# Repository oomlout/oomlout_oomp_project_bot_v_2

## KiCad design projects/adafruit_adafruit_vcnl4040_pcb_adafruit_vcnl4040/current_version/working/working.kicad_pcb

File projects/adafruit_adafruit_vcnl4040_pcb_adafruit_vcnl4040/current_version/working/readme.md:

# adafruit_vcnl4040_pcb
 
## summary 
* id: adafruit_adafruit_vcnl4040_pcb_adafruit_vcnl4040
* user: adafruit
* name: adafruit_vcnl4040_pcb
* board: adafruit_vcnl4040
* repo: https://github.com/adafruit/Adafruit-VCNL4040-PCB

* src_file_repo_sch: 
* src_file_repo_sch_link: https://github.com/adafruit/Adafruit-VCNL4040-PCB/tree/master/
* full details link: https://github.com/oomlout/oomlout_oomp_project_bot_v_2/tree/main/projects/adafruit_adafruit_vcnl4040_pcb_adafruit_vcnl4040/current_version/working  

## schematic  
  
[schematic (pdf)](working_schematic.pdf) 

## pcb  

[board (pdf)](working.pdf)  

## working_bom
| Id | Designator | Footprint | Quantity | Designation | Supplier and ref |  | None | 
| --- | --- | --- | --- | --- | --- | --- | --- | 
| 1 | FID4,FID3 | FIDUCIAL_1MM | 2 | FIDUCIAL_1MM |  |  | [''] | 
| 2 | D1 | CHIPLED_0603_NOOUTLINE | 1 | GREEN |  |  | [''] | 
| 3 | U$1,U$19,U$21,U$17 | MOUNTINGHOLE_2.5_PLATED | 4 | MOUNTINGHOLE2.5 |  |  | [''] | 
| 4 | U$22 | ADAFRUIT_3.5MM | 1 |  |  |  | [''] | 
| 5 | CONN4,CONN3 | JST_SH4 | 2 | STEMMA_I2C_QT |  |  | [''] | 
| 6 | C2,C3 | 0805-NO | 2 | 10uF |  |  | [''] | 
| 7 | C1 | 0603-NO | 1 | 0.1uF |  |  | [''] | 
| 8 | U2 | SOT23-5 | 1 | AP2112K-3.3 |  |  | [''] | 
| 9 | U3 | VISHAY_VCNL4040_4X2X1.1 | 1 | VCNL4040M3OE |  |  | [''] | 
| 10 | R1 | 0603-NO | 1 | 10K |  |  | [''] | 
| 11 | Q2 | SOT363 | 1 | BSS138 |  |  | [''] | 
| 12 | JP1 | 1X06_ROUND_70 | 1 |  |  |  | [''] | 
| 13 | R3 | RESPACK_4X0603 | 1 | 10K |  |  | [''] | 
| 14 | U$25 | PCBFEAT-REV-040 | 1 |  |  |  | [''] | 
| 15 | U$31,U$30 | STEMMAQT | 2 |  |  |  | [''] | 

## bom_schematic
| Ref | Qnty | Value | Cmp name | Footprint | Description | Vendor | DNP | 
| --- | --- | --- | --- | --- | --- | --- | --- | 
| C1 | 1 | 0.1uF | CAP_CERAMIC0603_NO | working:0603-NO |  |  |  | 
| C2, C3 | 2 | 10uF | CAP_CERAMIC0805-NOOUTLINE | working:0805-NO |  |  |  | 
| CONN3, CONN4 | 2 | STEMMA_I2C_QT | STEMMA_I2C_QT | working:JST_SH4 |  |  |  | 
| D1 | 1 | GREEN | LED0603_NOOUTLINE | working:CHIPLED_0603_NOOUTLINE |  |  |  | 
| FID3, FID4 | 2 | FIDUCIAL_1MM | FIDUCIAL_1MM | working:FIDUCIAL_1MM |  |  |  | 
| JP1 | 1 | HEADER-1X670MIL | HEADER-1X670MIL | working:1X06_ROUND_70 |  |  |  | 
| Q2 | 1 | BSS138 | MOSFET-N_DUAL | working:SOT363 |  |  |  | 
| R1 | 1 | 10K | RESISTOR_0603_NOOUT | working:0603-NO |  |  |  | 
| R3 | 1 | 10K | RESISTOR_4PACK | working:RESPACK_4X0603 |  |  |  | 
| U2 | 1 | AP2112K-3.3 | VREG_SOT23-5 | working:SOT23-5 |  |  |  | 
| U3 | 1 | VCNL4040M3OE | VCNL4040M3OE | working:VISHAY_VCNL4040_4X2X1.1 |  |  |  | 
| U$1, U$17, U$19, U$21 | 4 | MOUNTINGHOLE2.5 | MOUNTINGHOLE2.5 | working:MOUNTINGHOLE_2.5_PLATED |  |  |  | 

## mounting_holes
| x | y | package | value | ref | size | 
| --- | --- | --- | --- | --- | --- | 
| 0.0 | 12.7 | MOUNTINGHOLE_2.5_PLATED | MOUNTINGHOLE2.5 | U$1 | m3 | 
| 20.32 | 12.7 | MOUNTINGHOLE_2.5_PLATED | MOUNTINGHOLE2.5 | U$17 | m3 | 
| 0.0 | 0.0 | MOUNTINGHOLE_2.5_PLATED | MOUNTINGHOLE2.5 | U$19 | m3 | 
| 20.32 | 0.0 | MOUNTINGHOLE_2.5_PLATED | MOUNTINGHOLE2.5 | U$21 | m3 |

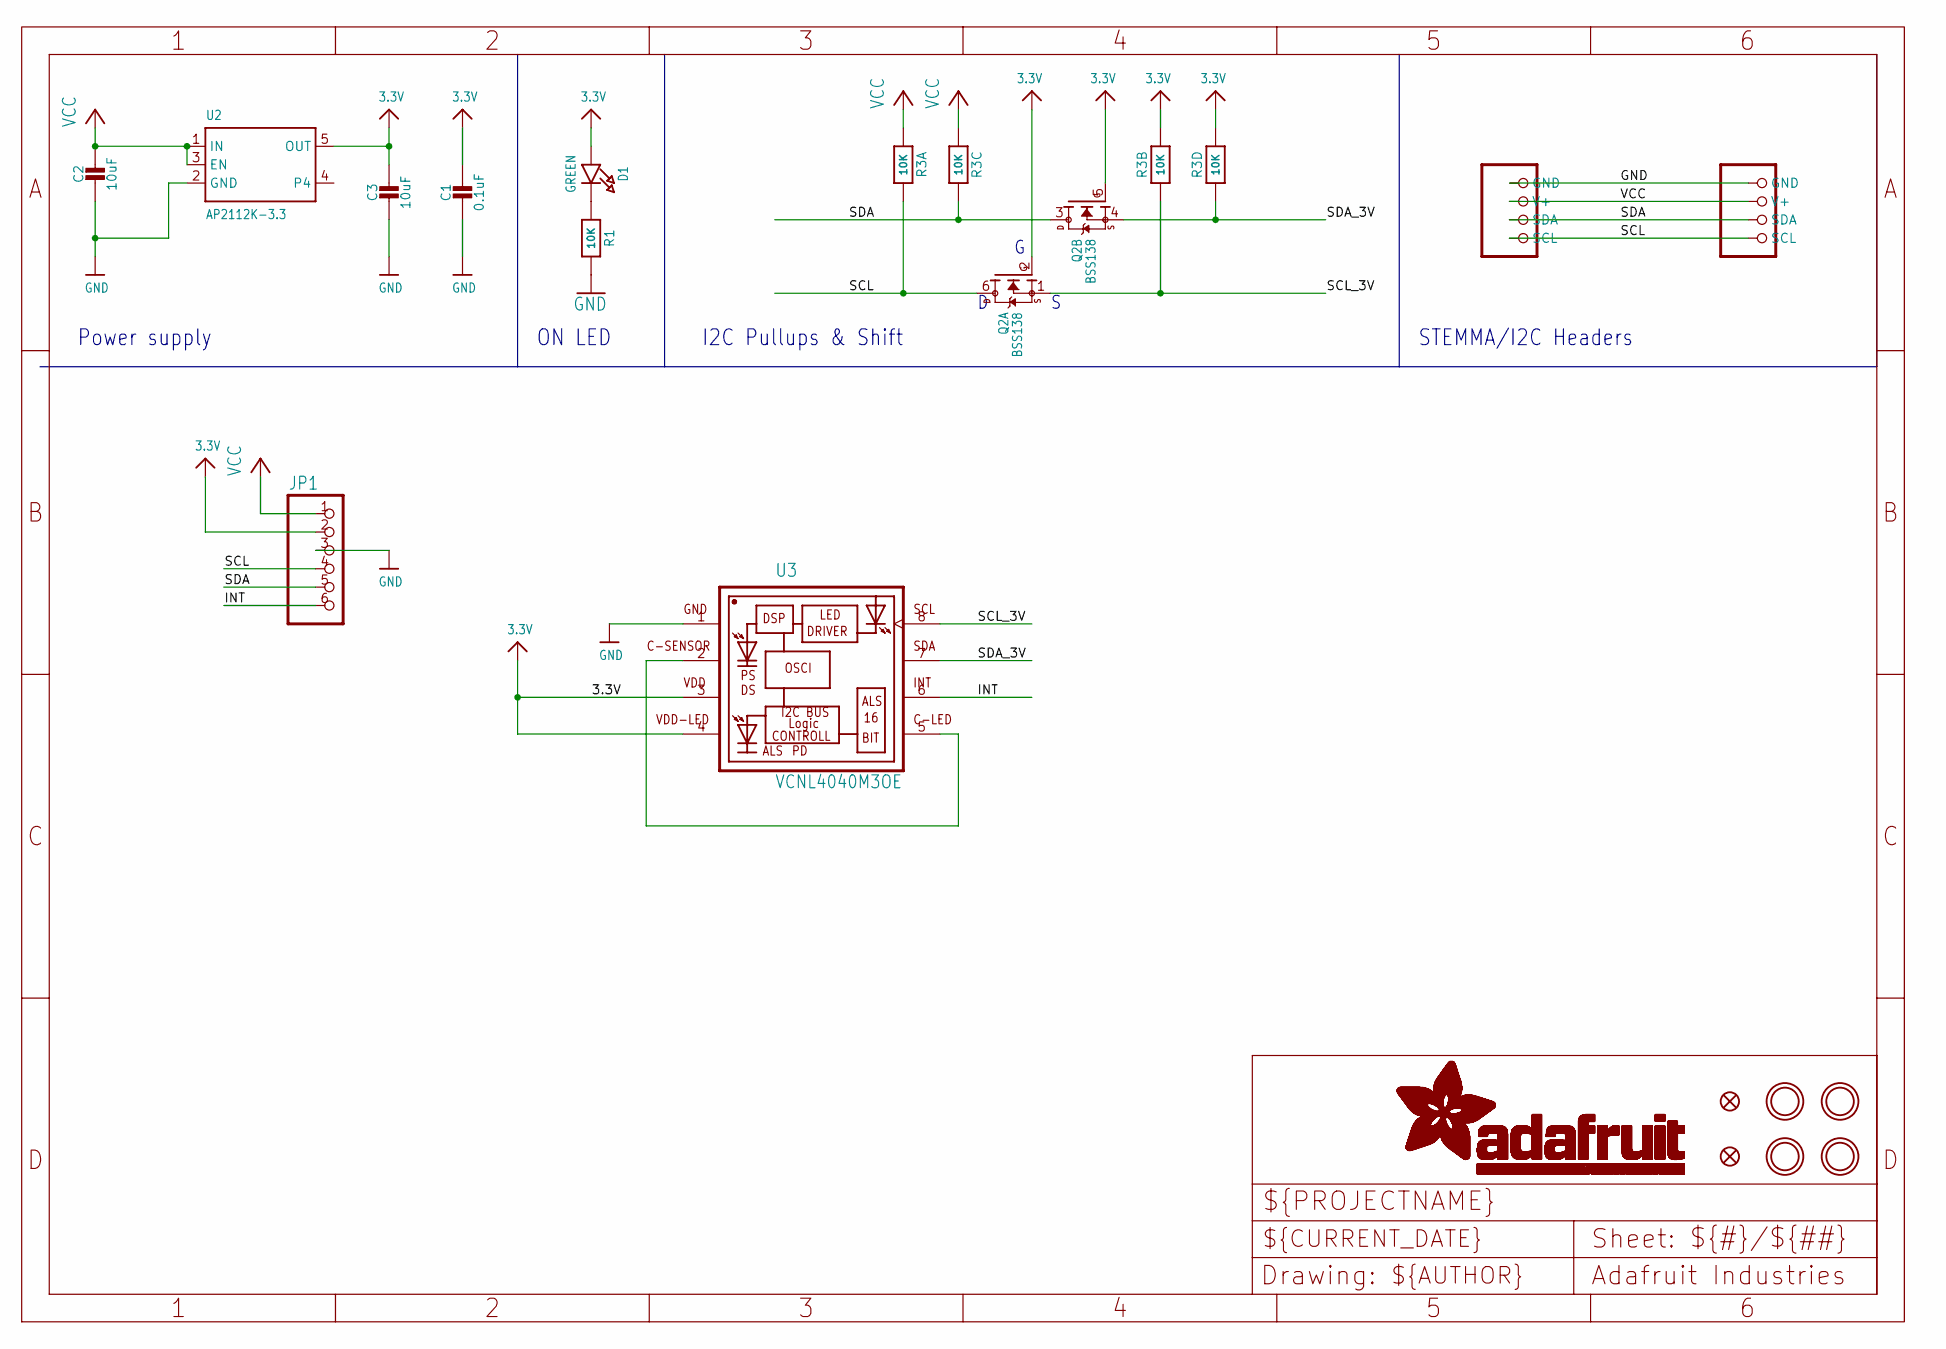
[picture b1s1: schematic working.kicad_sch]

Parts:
C1: 0.1uF; 0603-NO
C2, C3: 10uF; 0805-NO
CONN3, CONN4: STEMMA_I2C_QT; JST_SH4
D1: GREEN; CHIPLED_0603_NOOUTLINE
FID3, FID4: FIDUCIAL_1MM
JP1: HEADER-1X670MIL; 1X06_ROUND_70
Q2: BSS138; SOT363
R1: 10K; 0603-NO
R3: 10K; RESPACK_4X0603
U2: AP2112K-3.3; SOT23-5
U3: VCNL4040M3OE; VISHAY_VCNL4040_4X2X1.1
U$1, U$17, U$19, U$21: MOUNTINGHOLE2.5; MOUNTINGHOLE_2.5_PLATED

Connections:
3.3V: C1.1, C3.1, D1.A, JP1.2, Q2.2 (G), Q2.5 (G), R3.2 (1), R3.4 (1), U2.5 (OUT), U3.3 (VDD), U3.4 (VDD-LED)
CATHODE: U3.2 (C-SENSOR), U3.5 (C-LED)
GND: C1.2, C2.2, C3.2, CONN3.1 (GND), CONN4.1 (GND), JP1.3, R1.2, U2.2 (GND), U3.1 (GND)
INT: JP1.6, U3.6 (INT)
unnamed: D1.C, R1.1
SCL: CONN3.4 (SCL), CONN4.4 (SCL), JP1.4, Q2.6 (D), R3.8 (2)
SCL_3V: Q2.1 (S), R3.7 (2), U3.8 (SCL)
SDA: CONN3.3 (SDA), CONN4.3 (SDA), JP1.5, Q2.3 (D), R3.6 (2)
SDA_3V: Q2.4 (S), R3.5 (2), U3.7 (SDA)
VCC: C2.1, CONN3.2 (V+), CONN4.2 (V+), JP1.1, R3.1, R3.3 (1), U2.1 (IN), U2.3 (EN)

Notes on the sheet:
I2C Pullups & Shift
STEMMA/I2C Headers
ON LED
Power supply

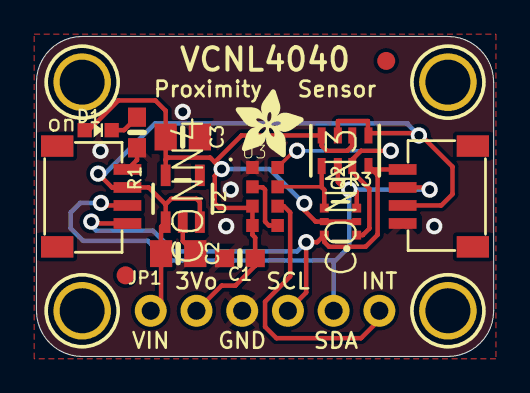
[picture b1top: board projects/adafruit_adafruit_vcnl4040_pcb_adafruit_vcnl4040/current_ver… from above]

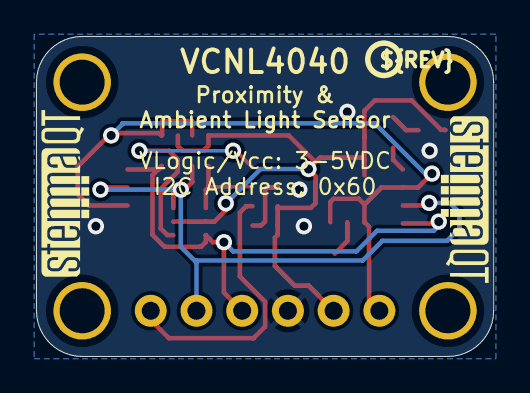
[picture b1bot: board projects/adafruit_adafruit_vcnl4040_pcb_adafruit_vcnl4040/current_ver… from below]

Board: 2 copper layers, 25.4 x 17.8 mm, 22 parts (3 on the bottom side), 10 nets.

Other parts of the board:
U$22: ADAFRUIT_3.5MM
U$25: PCBFEAT-REV-040
U$30, U$31: STEMMAQT

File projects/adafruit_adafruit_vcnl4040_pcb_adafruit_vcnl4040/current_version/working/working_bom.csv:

"Id";"Designator";"Footprint";"Quantity";"Designation";"Supplier and ref";
1;"FID4,FID3";"FIDUCIAL_1MM";2;"FIDUCIAL_1MM";;;
2;"D1";"CHIPLED_0603_NOOUTLINE";1;"GREEN";;;
3;"U$1,U$19,U$21,U$17";"MOUNTINGHOLE_2.5_PLATED";4;"MOUNTINGHOLE2.5";;;
4;"U$22";"ADAFRUIT_3.5MM";1;"";;;
5;"CONN4,CONN3";"JST_SH4";2;"STEMMA_I2C_QT";;;
6;"C2,C3";"0805-NO";2;"10uF";;;
7;"C1";"0603-NO";1;"0.1uF";;;
8;"U2";"SOT23-5";1;"AP2112K-3.3";;;
9;"U3";"VISHAY_VCNL4040_4X2X1.1";1;"VCNL4040M3OE";;;
10;"R1";"0603-NO";1;"10K";;;
11;"Q2";"SOT363";1;"BSS138";;;
12;"JP1";"1X06_ROUND_70";1;"";;;
13;"R3";"RESPACK_4X0603";1;"10K";;;
14;"U$25";"PCBFEAT-REV-040";1;"";;;
15;"U$31,U$30";"STEMMAQT";2;"";;;

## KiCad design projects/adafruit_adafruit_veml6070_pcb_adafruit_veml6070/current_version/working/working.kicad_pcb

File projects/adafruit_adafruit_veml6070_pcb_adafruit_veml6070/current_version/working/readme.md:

# adafruit_veml6070_pcb
 
## summary 
* id: adafruit_adafruit_veml6070_pcb_adafruit_veml6070
* user: adafruit
* name: adafruit_veml6070_pcb
* board: adafruit_veml6070
* repo: https://github.com/adafruit/Adafruit-VEML6070-PCB

* src_file_repo_sch: 
* src_file_repo_sch_link: https://github.com/adafruit/Adafruit-VEML6070-PCB/tree/master/
* full details link: https://github.com/oomlout/oomlout_oomp_project_bot_v_2/tree/main/projects/adafruit_adafruit_veml6070_pcb_adafruit_veml6070/current_version/working  

## schematic  
  
[schematic (pdf)](working_schematic.pdf) 

## pcb  

[board (pdf)](working.pdf)  

## working_bom
| Id | Designator | Footprint | Quantity | Designation | Supplier and ref |  | None | 
| --- | --- | --- | --- | --- | --- | --- | --- | 
| 1 | FID1 | FIDUCIAL_1MM | 1 | FIDUCIAL" |  |  | [''] | 
| 2 | U$11,U$10 | MOUNTINGHOLE_2.5_PLATED | 2 | MOUNTINGHOLE2.5 |  |  | [''] | 
| 3 | C1 | 0805-NO | 1 | 10uF |  |  | [''] | 
| 4 | U1 | VEML6070 | 1 | VEML6070 |  |  | [''] | 
| 5 | JP1 | 1X05_ROUND_70 | 1 |  |  |  | [''] | 
| 6 | R1,R4,R2 | 0805-NO | 3 | 10K |  |  | [''] | 
| 7 | R3 | 0805-NO | 1 | 270K |  |  | [''] | 
| 8 | U$2 | PCBFEAT-REV-040 | 1 |  |  |  | [''] | 
| 9 | U$14 | ADAFRUIT_2.5MM | 1 |  |  |  | [''] | 

## bom_schematic
| Ref | Qnty | Value | Cmp name | Footprint | Description | Vendor | DNP | 
| --- | --- | --- | --- | --- | --- | --- | --- | 
| C1 | 1 | 10uF | CAP_CERAMIC0805-NOOUTLINE | working:0805-NO |  |  |  | 
| FID1 | 1 | FIDUCIAL"" | FIDUCIAL{dblquote}{dblquote} | working:FIDUCIAL_1MM |  |  |  | 
| JP1 | 1 | HEADER-1X570MIL | HEADER-1X570MIL | working:1X05_ROUND_70 |  |  |  | 
| R1, R2, R4 | 3 | 10K | RESISTOR0805_NOOUTLINE | working:0805-NO |  |  |  | 
| R3 | 1 | 270K | RESISTOR0805_NOOUTLINE | working:0805-NO |  |  |  | 
| U1 | 1 | VEML6070 | UV_VEML6070 | working:VEML6070 |  |  |  | 
| U$10, U$11 | 2 | MOUNTINGHOLE2.5 | MOUNTINGHOLE2.5 | working:MOUNTINGHOLE_2.5_PLATED |  |  |  | 

## mounting_holes
| x | y | package | value | ref | size | 
| --- | --- | --- | --- | --- | --- | 
| 0.0 | 0.0 | MOUNTINGHOLE_2.5_PLATED | MOUNTINGHOLE2.5 | U$10 | m3 | 
| 7.62 | 0.0 | MOUNTINGHOLE_2.5_PLATED | MOUNTINGHOLE2.5 | U$11 | m3 |

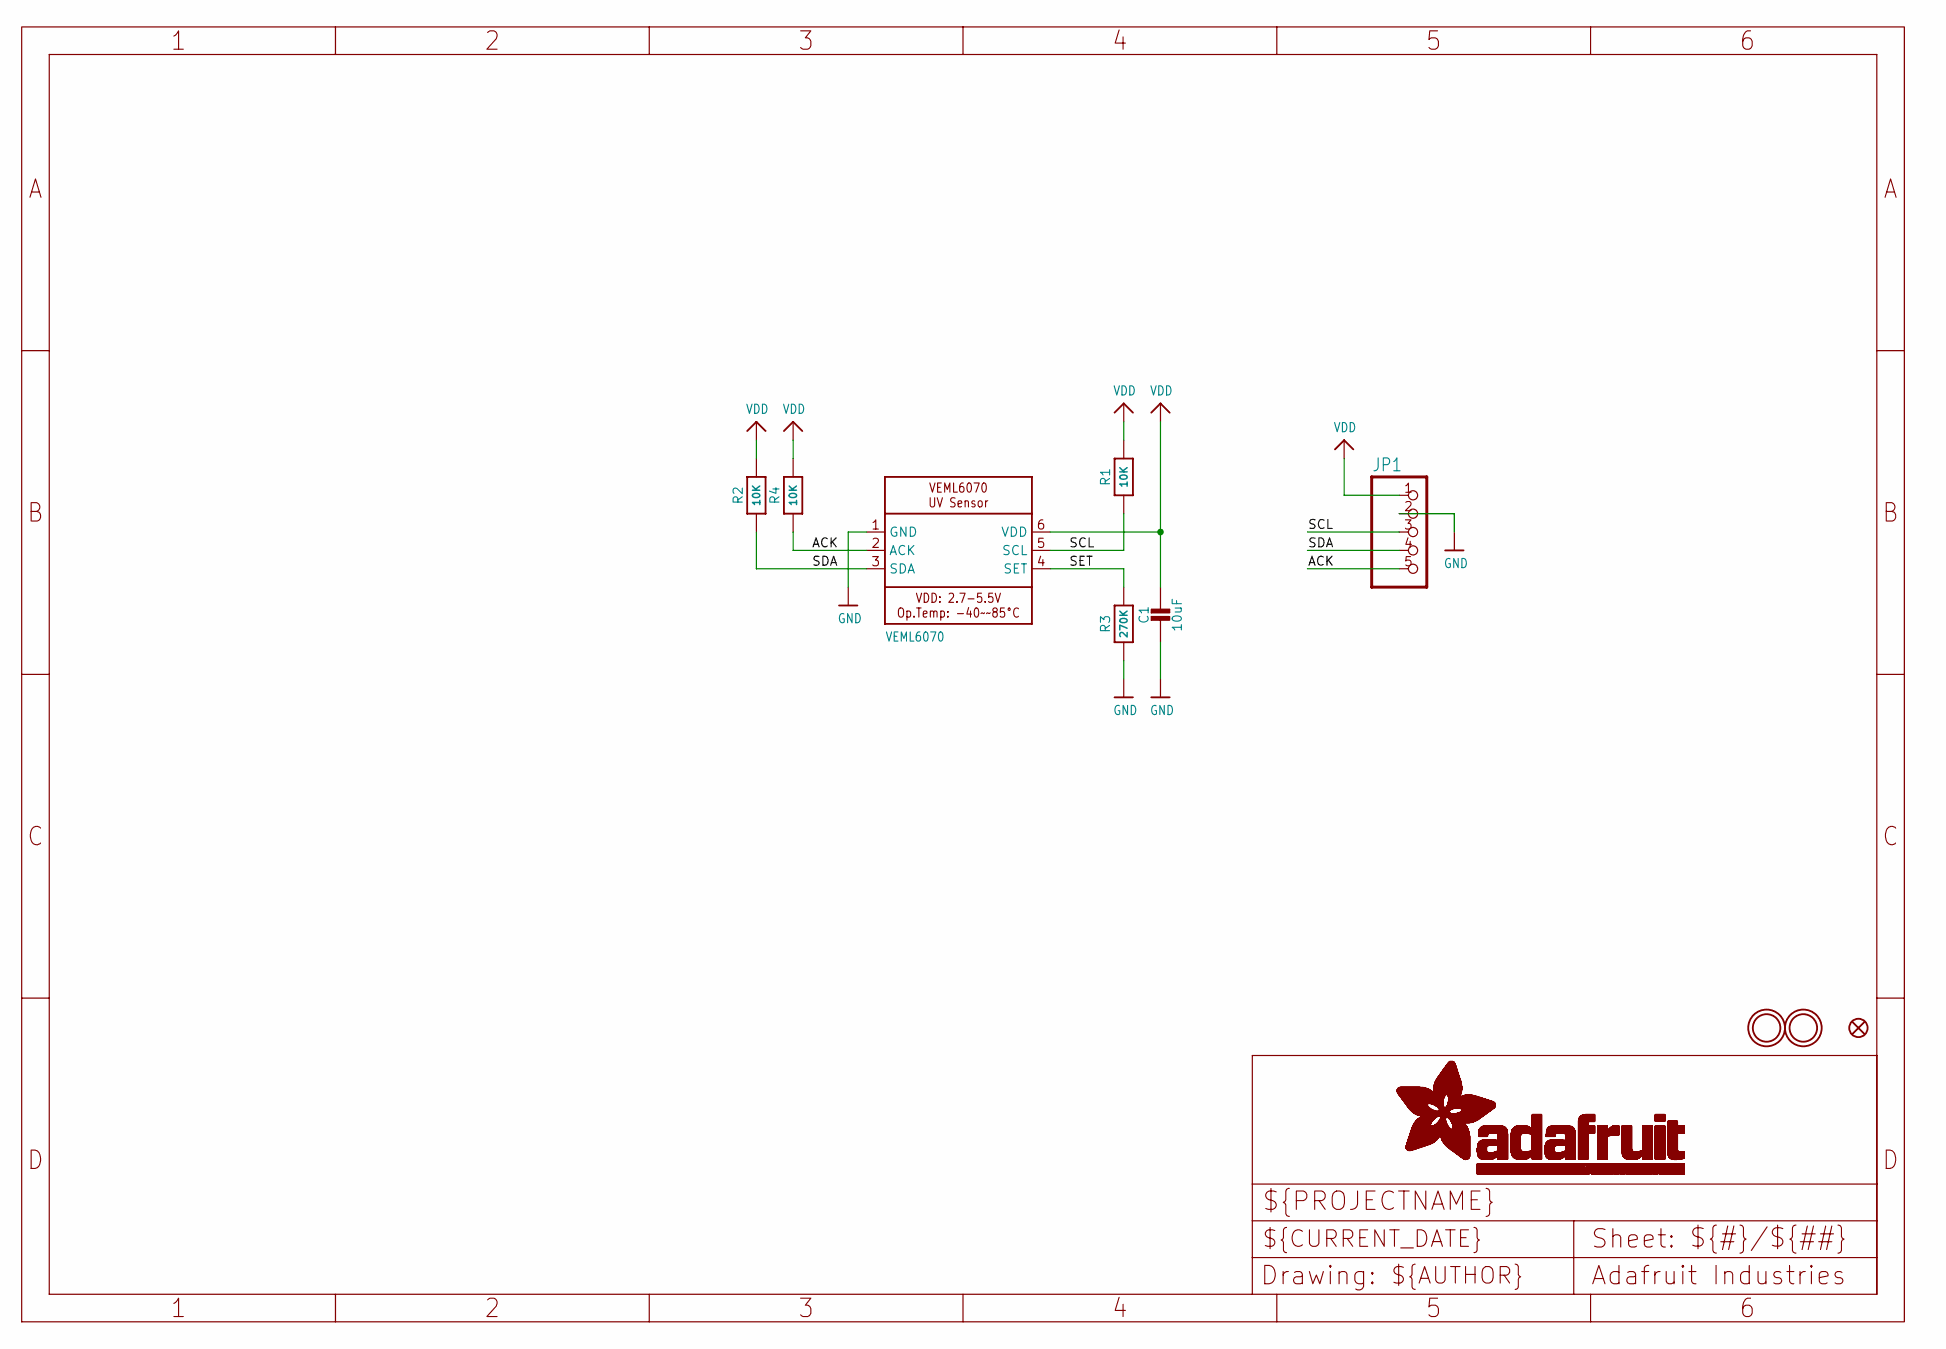
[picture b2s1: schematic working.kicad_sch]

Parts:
C1: 10uF; 0805-NO
FID1: FIDUCIAL""; FIDUCIAL_1MM
JP1: HEADER-1X570MIL; 1X05_ROUND_70
R1, R2, R4: 10K; 0805-NO
R3: 270K; 0805-NO
U1: VEML6070
U$10, U$11: MOUNTINGHOLE2.5; MOUNTINGHOLE_2.5_PLATED

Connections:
ACK: JP1.5, R4.1, U1.2 (ACK)
GND: C1.2, JP1.2, R3.1, U1.1 (GND)
SCL: JP1.3, R1.1, U1.5 (SCL)
SDA: JP1.4, R2.1, U1.3 (SDA)
SET: R3.2, U1.4 (SET)
VDD: C1.1, JP1.1, R1.2, R2.2, R4.2, U1.6 (VDD)

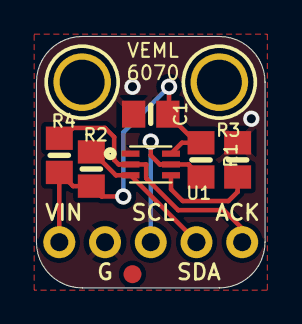
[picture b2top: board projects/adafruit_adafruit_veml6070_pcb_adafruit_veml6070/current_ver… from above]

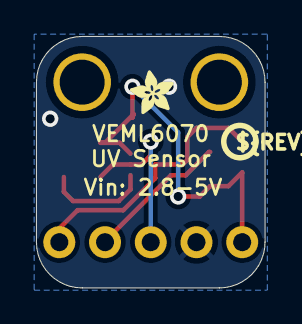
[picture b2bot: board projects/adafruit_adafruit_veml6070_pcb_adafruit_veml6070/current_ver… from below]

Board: 2 copper layers, 12.7 x 14.0 mm, 12 parts (2 on the bottom side), 6 nets.

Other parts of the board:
U$2: PCBFEAT-REV-040
U$14: ADAFRUIT_2.5MM

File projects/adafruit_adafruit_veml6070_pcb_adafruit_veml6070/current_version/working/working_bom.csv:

"Id";"Designator";"Footprint";"Quantity";"Designation";"Supplier and ref";
1;"FID1";"FIDUCIAL_1MM";1;"FIDUCIAL""";;;
2;"U$11,U$10";"MOUNTINGHOLE_2.5_PLATED";2;"MOUNTINGHOLE2.5";;;
3;"C1";"0805-NO";1;"10uF";;;
4;"U1";"VEML6070";1;"VEML6070";;;
5;"JP1";"1X05_ROUND_70";1;"";;;
6;"R1,R4,R2";"0805-NO";3;"10K";;;
7;"R3";"0805-NO";1;"270K";;;
8;"U$2";"PCBFEAT-REV-040";1;"";;;
9;"U$14";"ADAFRUIT_2.5MM";1;"";;;

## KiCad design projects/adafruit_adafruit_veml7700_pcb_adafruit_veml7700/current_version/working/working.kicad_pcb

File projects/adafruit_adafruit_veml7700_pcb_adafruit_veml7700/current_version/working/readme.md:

# adafruit_veml7700_pcb
 
## summary 
* id: adafruit_adafruit_veml7700_pcb_adafruit_veml7700
* user: adafruit
* name: adafruit_veml7700_pcb
* board: adafruit_veml7700
* repo: https://github.com/adafruit/Adafruit-VEML7700-PCB

* src_file_repo_sch: 
* src_file_repo_sch_link: https://github.com/adafruit/Adafruit-VEML7700-PCB/tree/master/
* full details link: https://github.com/oomlout/oomlout_oomp_project_bot_v_2/tree/main/projects/adafruit_adafruit_veml7700_pcb_adafruit_veml7700/current_version/working  

## schematic  
  
[schematic (pdf)](working_schematic.pdf) 

## pcb  

[board (pdf)](working.pdf)  

## working_bom
| Id | Designator | Footprint | Quantity | Designation | Supplier and ref |  | None | 
| --- | --- | --- | --- | --- | --- | --- | --- | 
| 1 | FID4,FID3 | FIDUCIAL_1MM | 2 | FIDUCIAL_1MM |  |  | [''] | 
| 2 | U$4,U$22 | ADAFRUIT_3.5MM | 2 |  |  |  | [''] | 
| 3 | U$21,U$17,U$1,U$19 | MOUNTINGHOLE_2.5_PLATED | 4 | MOUNTINGHOLE2.5 |  |  | [''] | 
| 4 | C3,C2 | 0805-NO | 2 | 10uF |  |  | [''] | 
| 5 | Q2 | SOT363 | 1 | BSS138 |  |  | [''] | 
| 6 | JP2 | 1X05_ROUND | 1 |  |  |  | [''] | 
| 7 | U2 | SOT23-5 | 1 | AP2112K-3.3 |  |  | [''] | 
| 8 | R1 | 0603-NO | 1 | 47K |  |  | [''] | 
| 9 | R3 | RESPACK_4X0603 | 1 | 4.7K |  |  | [''] | 
| 10 | C1 | 0603-NO | 1 | 0.1uF |  |  | [''] | 
| 11 | CONN4,CONN3 | JST_SH4 | 2 | STEMMA_I2C_QT |  |  | [''] | 
| 12 | IC1 | VEML7700 | 1 | VEML7700 |  |  | [''] | 
| 13 | D1 | CHIPLED_0603_NOOUTLINE | 1 | GREEN |  |  | [''] | 
| 14 | U$25 | PCBFEAT-REV-040 | 1 |  |  |  | [''] | 
| 15 | U$30,U$31 | STEMMAQT | 2 |  |  |  | [''] | 
| 16 | U$2 | KATTNI_STOP | 1 |  |  |  | [''] | 
| 17 | SJ1 | SOLDERJUMPER_CLOSEDWIRE | 1 |  |  |  | [''] | 

## bom_schematic
| Ref | Qnty | Value | Cmp name | Footprint | Description | Vendor | DNP | 
| --- | --- | --- | --- | --- | --- | --- | --- | 
| C1 | 1 | 0.1uF | CAP_CERAMIC0603_NO | working:0603-NO |  |  |  | 
| C2, C3 | 2 | 10uF | CAP_CERAMIC0805-NOOUTLINE | working:0805-NO |  |  |  | 
| CONN3, CONN4 | 2 | STEMMA_I2C_QT | STEMMA_I2C_QT | working:JST_SH4 |  |  |  | 
| D1 | 1 | GREEN | LED0603_NOOUTLINE | working:CHIPLED_0603_NOOUTLINE |  |  |  | 
| FID3, FID4 | 2 | FIDUCIAL_1MM | FIDUCIAL_1MM | working:FIDUCIAL_1MM |  |  |  | 
| IC1 | 1 | VEML7700 | VEML7700 | working:VEML7700 |  |  |  | 
| JP2 | 1 | HEADER-1X5ROUND | HEADER-1X5ROUND | working:1X05_ROUND |  |  |  | 
| Q2 | 1 | BSS138 | MOSFET-N_DUAL | working:SOT363 |  |  |  | 
| R1 | 1 | 47K | RESISTOR_0603_NOOUT | working:0603-NO |  |  |  | 
| R3 | 1 | 4.7K | RESISTOR_4PACK | working:RESPACK_4X0603 |  |  |  | 
| SJ1 | 1 | SOLDERJUMPER_CLOSED | SOLDERJUMPER_CLOSED | working:SOLDERJUMPER_CLOSEDWIRE |  |  |  | 
| U2 | 1 | AP2112K-3.3 | VREG_SOT23-5 | working:SOT23-5 |  |  |  | 
| U$1, U$17, U$19, U$21 | 4 | MOUNTINGHOLE2.5 | MOUNTINGHOLE2.5 | working:MOUNTINGHOLE_2.5_PLATED |  |  |  | 

## mounting_holes
| x | y | package | value | ref | size | 
| --- | --- | --- | --- | --- | --- | 
| 0.0 | 12.7 | MOUNTINGHOLE_2.5_PLATED | MOUNTINGHOLE2.5 | U$1 | m3 | 
| 20.32 | 12.7 | MOUNTINGHOLE_2.5_PLATED | MOUNTINGHOLE2.5 | U$17 | m3 | 
| 0.0 | 0.0 | MOUNTINGHOLE_2.5_PLATED | MOUNTINGHOLE2.5 | U$19 | m3 | 
| 20.32 | 0.0 | MOUNTINGHOLE_2.5_PLATED | MOUNTINGHOLE2.5 | U$21 | m3 |

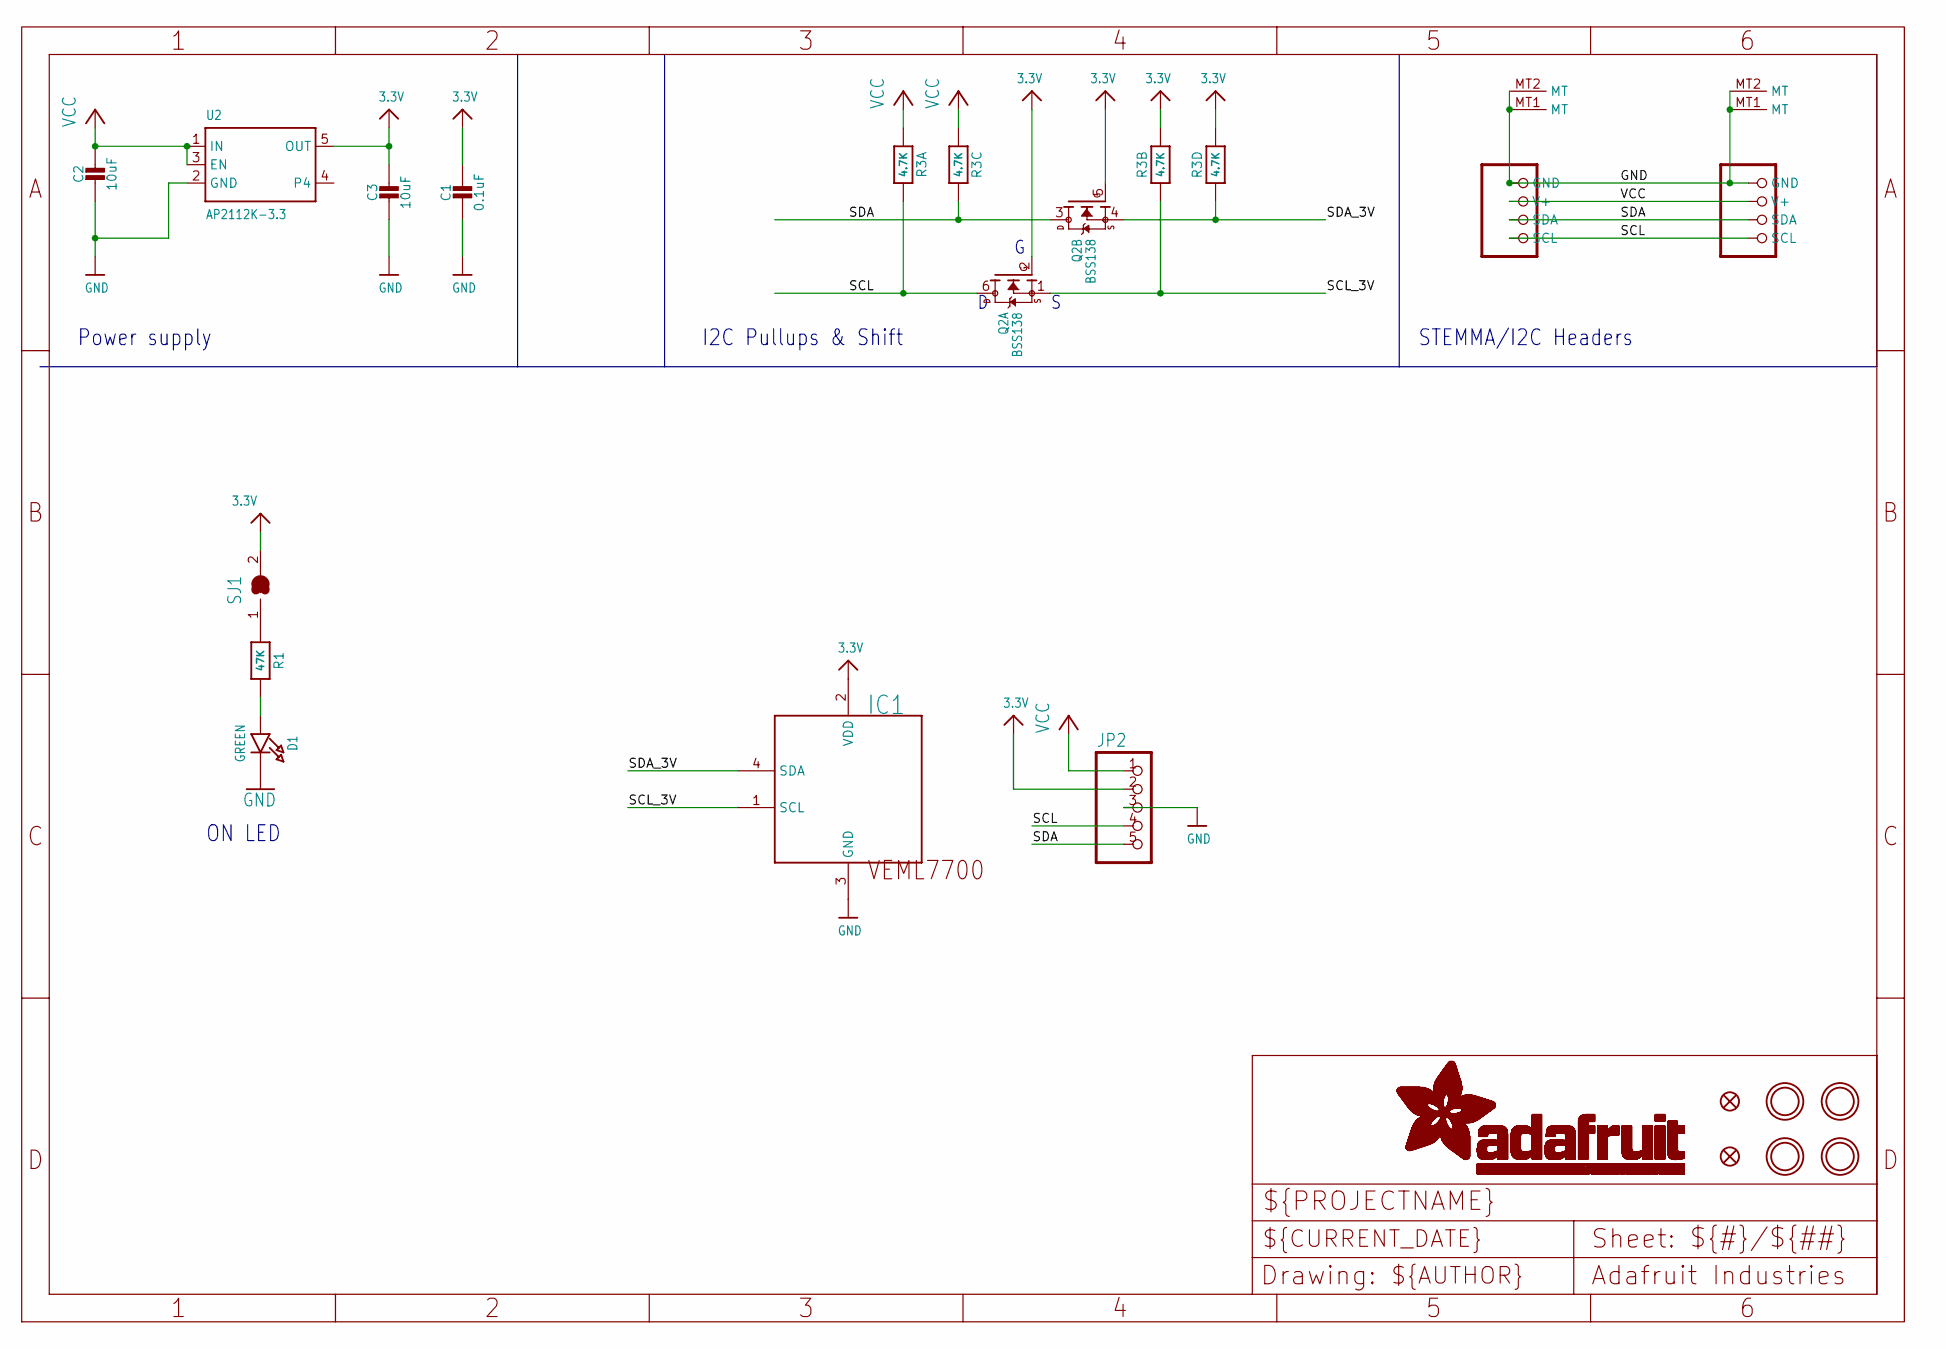
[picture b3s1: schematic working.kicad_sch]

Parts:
C1: 0.1uF; 0603-NO
C2, C3: 10uF; 0805-NO
CONN3, CONN4: STEMMA_I2C_QT; JST_SH4
D1: GREEN; CHIPLED_0603_NOOUTLINE
FID3, FID4: FIDUCIAL_1MM
IC1: VEML7700
JP2: HEADER-1X5ROUND; 1X05_ROUND
Q2: BSS138; SOT363
R1: 47K; 0603-NO
R3: 4.7K; RESPACK_4X0603
SJ1: SOLDERJUMPER_CLOSED; SOLDERJUMPER_CLOSEDWIRE
U2: AP2112K-3.3; SOT23-5
U$1, U$17, U$19, U$21: MOUNTINGHOLE2.5; MOUNTINGHOLE_2.5_PLATED

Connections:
3.3V: C1.1, C3.1, IC1.2 (VDD), JP2.2, Q2.2 (G), Q2.5 (G), R3.2 (1), R3.4 (1), SJ1.2, U2.5 (OUT)
GND: C1.2, C2.2, C3.2, CONN3.1 (GND), CONN3.MT1 (MT), CONN3.MT2 (MT), CONN4.1 (GND), CONN4.MT1 (MT), CONN4.MT2 (MT), D1.C, IC1.3 (GND), JP2.3, U2.2 (GND)
unnamed: D1.A, R1.2
unnamed: R1.1, SJ1.1
SCL: CONN3.4 (SCL), CONN4.4 (SCL), JP2.4, Q2.6 (D), R3.8 (2)
SCL_3V: IC1.1 (SCL), Q2.1 (S), R3.7 (2)
SDA: CONN3.3 (SDA), CONN4.3 (SDA), JP2.5, Q2.3 (D), R3.6 (2)
SDA_3V: IC1.4 (SDA), Q2.4 (S), R3.5 (2)
VCC: C2.1, CONN3.2 (V+), CONN4.2 (V+), JP2.1, R3.1, R3.3 (1), U2.1 (IN), U2.3 (EN)

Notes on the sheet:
Power supply
ON LED
I2C Pullups & Shift
STEMMA/I2C Headers

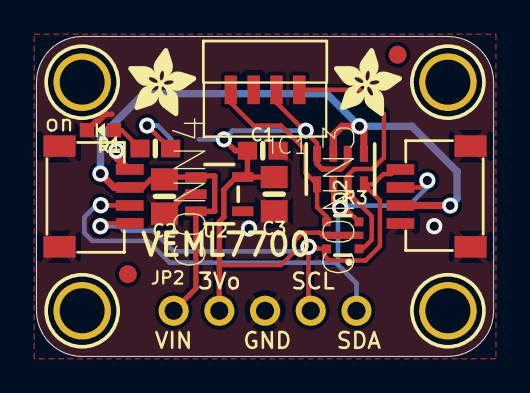
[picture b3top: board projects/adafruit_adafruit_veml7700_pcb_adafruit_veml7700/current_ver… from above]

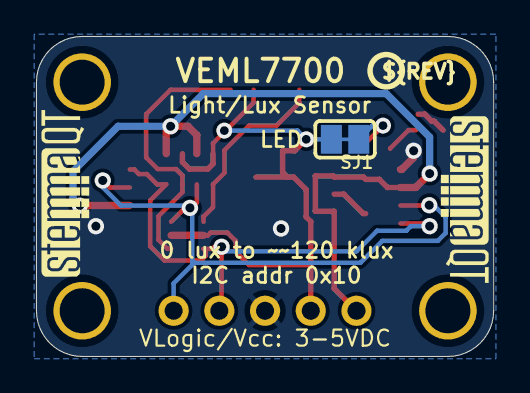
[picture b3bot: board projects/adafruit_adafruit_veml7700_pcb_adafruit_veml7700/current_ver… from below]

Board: 2 copper layers, 25.4 x 17.8 mm, 25 parts (5 on the bottom side), 9 nets.

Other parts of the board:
U$2: KATTNI_STOP
U$4, U$22: ADAFRUIT_3.5MM
U$25: PCBFEAT-REV-040
U$30, U$31: STEMMAQT

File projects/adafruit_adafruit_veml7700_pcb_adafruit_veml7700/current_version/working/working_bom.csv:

"Id";"Designator";"Footprint";"Quantity";"Designation";"Supplier and ref";
1;"FID4,FID3";"FIDUCIAL_1MM";2;"FIDUCIAL_1MM";;;
2;"U$4,U$22";"ADAFRUIT_3.5MM";2;"";;;
3;"U$21,U$17,U$1,U$19";"MOUNTINGHOLE_2.5_PLATED";4;"MOUNTINGHOLE2.5";;;
4;"C3,C2";"0805-NO";2;"10uF";;;
5;"Q2";"SOT363";1;"BSS138";;;
6;"JP2";"1X05_ROUND";1;"";;;
7;"U2";"SOT23-5";1;"AP2112K-3.3";;;
8;"R1";"0603-NO";1;"47K";;;
9;"R3";"RESPACK_4X0603";1;"4.7K";;;
10;"C1";"0603-NO";1;"0.1uF";;;
11;"CONN4,CONN3";"JST_SH4";2;"STEMMA_I2C_QT";;;
12;"IC1";"VEML7700";1;"VEML7700";;;
13;"D1";"CHIPLED_0603_NOOUTLINE";1;"GREEN";;;
14;"U$25";"PCBFEAT-REV-040";1;"";;;
15;"U$30,U$31";"STEMMAQT";2;"";;;
16;"U$2";"KATTNI_STOP";1;"";;;
17;"SJ1";"SOLDERJUMPER_CLOSEDWIRE";1;"";;;

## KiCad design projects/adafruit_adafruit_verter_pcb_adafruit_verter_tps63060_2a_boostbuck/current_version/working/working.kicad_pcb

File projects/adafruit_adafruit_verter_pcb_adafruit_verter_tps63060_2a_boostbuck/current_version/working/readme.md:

# adafruit_verter_pcb
 
## summary 
* id: adafruit_adafruit_verter_pcb_adafruit_verter_tps63060_2a_boostbuck
* user: adafruit
* name: adafruit_verter_pcb
* board: adafruit_verter_tps63060_2a_boostbuck
* repo: https://github.com/adafruit/Adafruit-Verter-PCB

* src_file_repo_sch: 
* src_file_repo_sch_link: https://github.com/adafruit/Adafruit-Verter-PCB/tree/master/
* full details link: https://github.com/oomlout/oomlout_oomp_project_bot_v_2/tree/main/projects/adafruit_adafruit_verter_pcb_adafruit_verter_tps63060_2a_boostbuck/current_version/working  

## schematic  
  
[schematic (pdf)](working_schematic.pdf) 

## pcb  

[board (pdf)](working.pdf)  

## working_bom
| Id | Designator | Footprint | Quantity | Designation | Supplier and ref |  | None | 
| --- | --- | --- | --- | --- | --- | --- | --- | 
| 1 | R11,R9 | 0805-NO | 2 | 75K 1% |  |  | [''] | 
| 2 | R5,R6,R2 | 0805-NO | 3 | 105K |  |  | [''] | 
| 3 | U$23,U$22 | SYMBOL_PLUS | 2 |  |  |  | [''] | 
| 4 | R12,R10 | 0805-NO | 2 | 49.9K 1% |  |  | [''] | 
| 5 | X1,X2 | TERMBLOCK_1X2-3.5MM | 2 |  |  |  | [''] | 
| 6 | C5,C6,C7 | 0805-NO | 3 | 22uF/10V X5R |  |  | [''] | 
| 7 | C4 | 0805-NO | 1 | 10pF |  |  | [''] | 
| 8 | R3,R1 | 0805-NO | 2 | 1M |  |  | [''] | 
| 9 | CN1 | USB_HOST-PTH | 1 | USBA_FEMALE |  |  | [''] | 
| 10 | C8 | 0805-NO | 1 | 1uF/10V X5R |  |  | [''] | 
| 11 | D1 | CHIPLED_0805_NOOUTLINE | 1 | GREEN |  |  | [''] | 
| 12 | U$15,U$17 | MOUNTINGHOLE_2.5_PLATED | 2 | MOUNTINGHOLE2.5 |  |  | [''] | 
| 13 | U$38 | PCBFEAT-REV-040 | 1 |  |  |  | [''] | 
| 14 | C2,C1 | 0805-NO | 2 | 10uF/16V X5R |  |  | [''] | 
| 15 | Q1 | SOT23-WIDE | 1 | BSS138 |  |  | [''] | 
| 16 | U$24,U$25 | SYMBOL_MINUS | 2 |  |  |  | [''] | 
| 17 | FID2,FID1 | FIDUCIAL_1MM | 2 | FIDUCIAL" |  |  | [''] | 
| 18 | U1 | PWSON-N10 | 1 | TPS63060 |  |  | [''] | 
| 19 | L1 | INDUCTOR_5X5MM_TDK_VLC5045 | 1 | NRS5030T1R0NMGJ  |  |  | [''] | 
| 20 | JP1 | 1X07_ROUND_70 | 1 |  |  |  | [''] | 
| 21 | R4 | 0805-NO | 1 | 1K |  |  | [''] | 
| 22 | U$27 | ADAFRUIT_3.5MM | 1 |  |  |  | [''] | 
| 23 | C3 | 0805-NO | 1 | 0.1uF |  |  | [''] | 
| 24 | U$37 | VERTERLOGO | 1 |  |  |  | [''] | 

## bom_schematic
| Ref | Qnty | Value | Cmp name | Footprint | Description | Vendor | DNP | 
| --- | --- | --- | --- | --- | --- | --- | --- | 
| C1, C2 | 2 | 10uF/16V X5R | CAP_CERAMIC0805-NOOUTLINE | working:0805-NO |  |  |  | 
| C3 | 1 | 0.1uF | CAP_CERAMIC0805-NOOUTLINE | working:0805-NO |  |  |  | 
| C4 | 1 | 10pF | CAP_CERAMIC0805-NOOUTLINE | working:0805-NO |  |  |  | 
| C5, C6, C7 | 3 | 22uF/10V X5R | CAP_CERAMIC0805-NOOUTLINE | working:0805-NO |  |  |  | 
| C8 | 1 | 1uF/10V X5R | CAP_CERAMIC0805-NOOUTLINE | working:0805-NO |  |  |  | 
| CN1 | 1 | USBA_FEMALE | USB_TYPEAPTHFML | working:USB_HOST-PTH |  |  |  | 
| D1 | 1 | GREEN | LED0805_NOOUTLINE | working:CHIPLED_0805_NOOUTLINE |  |  |  | 
| FID1, FID2 | 2 | FIDUCIAL"" | FIDUCIAL{dblquote}{dblquote} | working:FIDUCIAL_1MM |  |  |  | 
| JP1 | 1 | HEADER-1X770MIL | HEADER-1X770MIL | working:1X07_ROUND_70 |  |  |  | 
| L1 | 1 | NRS5030T1R0NMGJ  | INDUCTORTDK_VLC5045 | working:INDUCTOR_5X5MM_TDK_VLC5045 |  |  |  | 
| Q1 | 1 | BSS138 | MOSFET-NWIDE | working:SOT23-WIDE |  |  |  | 
| R1, R3 | 2 | 1M | RESISTOR0805_NOOUTLINE | working:0805-NO |  |  |  | 
| R2, R5, R6 | 3 | 105K | RESISTOR0805_NOOUTLINE | working:0805-NO |  |  |  | 
| R4 | 1 | 1K | RESISTOR0805_NOOUTLINE | working:0805-NO |  |  |  | 
| R9, R11 | 2 | 75K 1% | RESISTOR0805_NOOUTLINE | working:0805-NO |  |  |  | 
| R10, R12 | 2 | 49.9K 1% | RESISTOR0805_NOOUTLINE | working:0805-NO |  |  |  | 
| U1 | 1 | TPS63060 | VREG_TPS63060/1 | working:PWSON-N10 |  |  |  | 
| U$15, U$17 | 2 | MOUNTINGHOLE2.5 | MOUNTINGHOLE2.5 | working:MOUNTINGHOLE_2.5_PLATED |  |  |  | 
| X1, X2 | 2 | TERMBLOCK_1X2 | TERMBLOCK_1X2 | working:TERMBLOCK_1X2-3.5MM |  |  |  | 

## mounting_holes
| x | y | package | value | ref | size | 
| --- | --- | --- | --- | --- | --- | 
| 0.0 | 0.0 | MOUNTINGHOLE_2.5_PLATED | MOUNTINGHOLE2.5 | U$15 | m3 | 
| 0.0 | 13.97 | MOUNTINGHOLE_2.5_PLATED | MOUNTINGHOLE2.5 | U$17 | m3 |

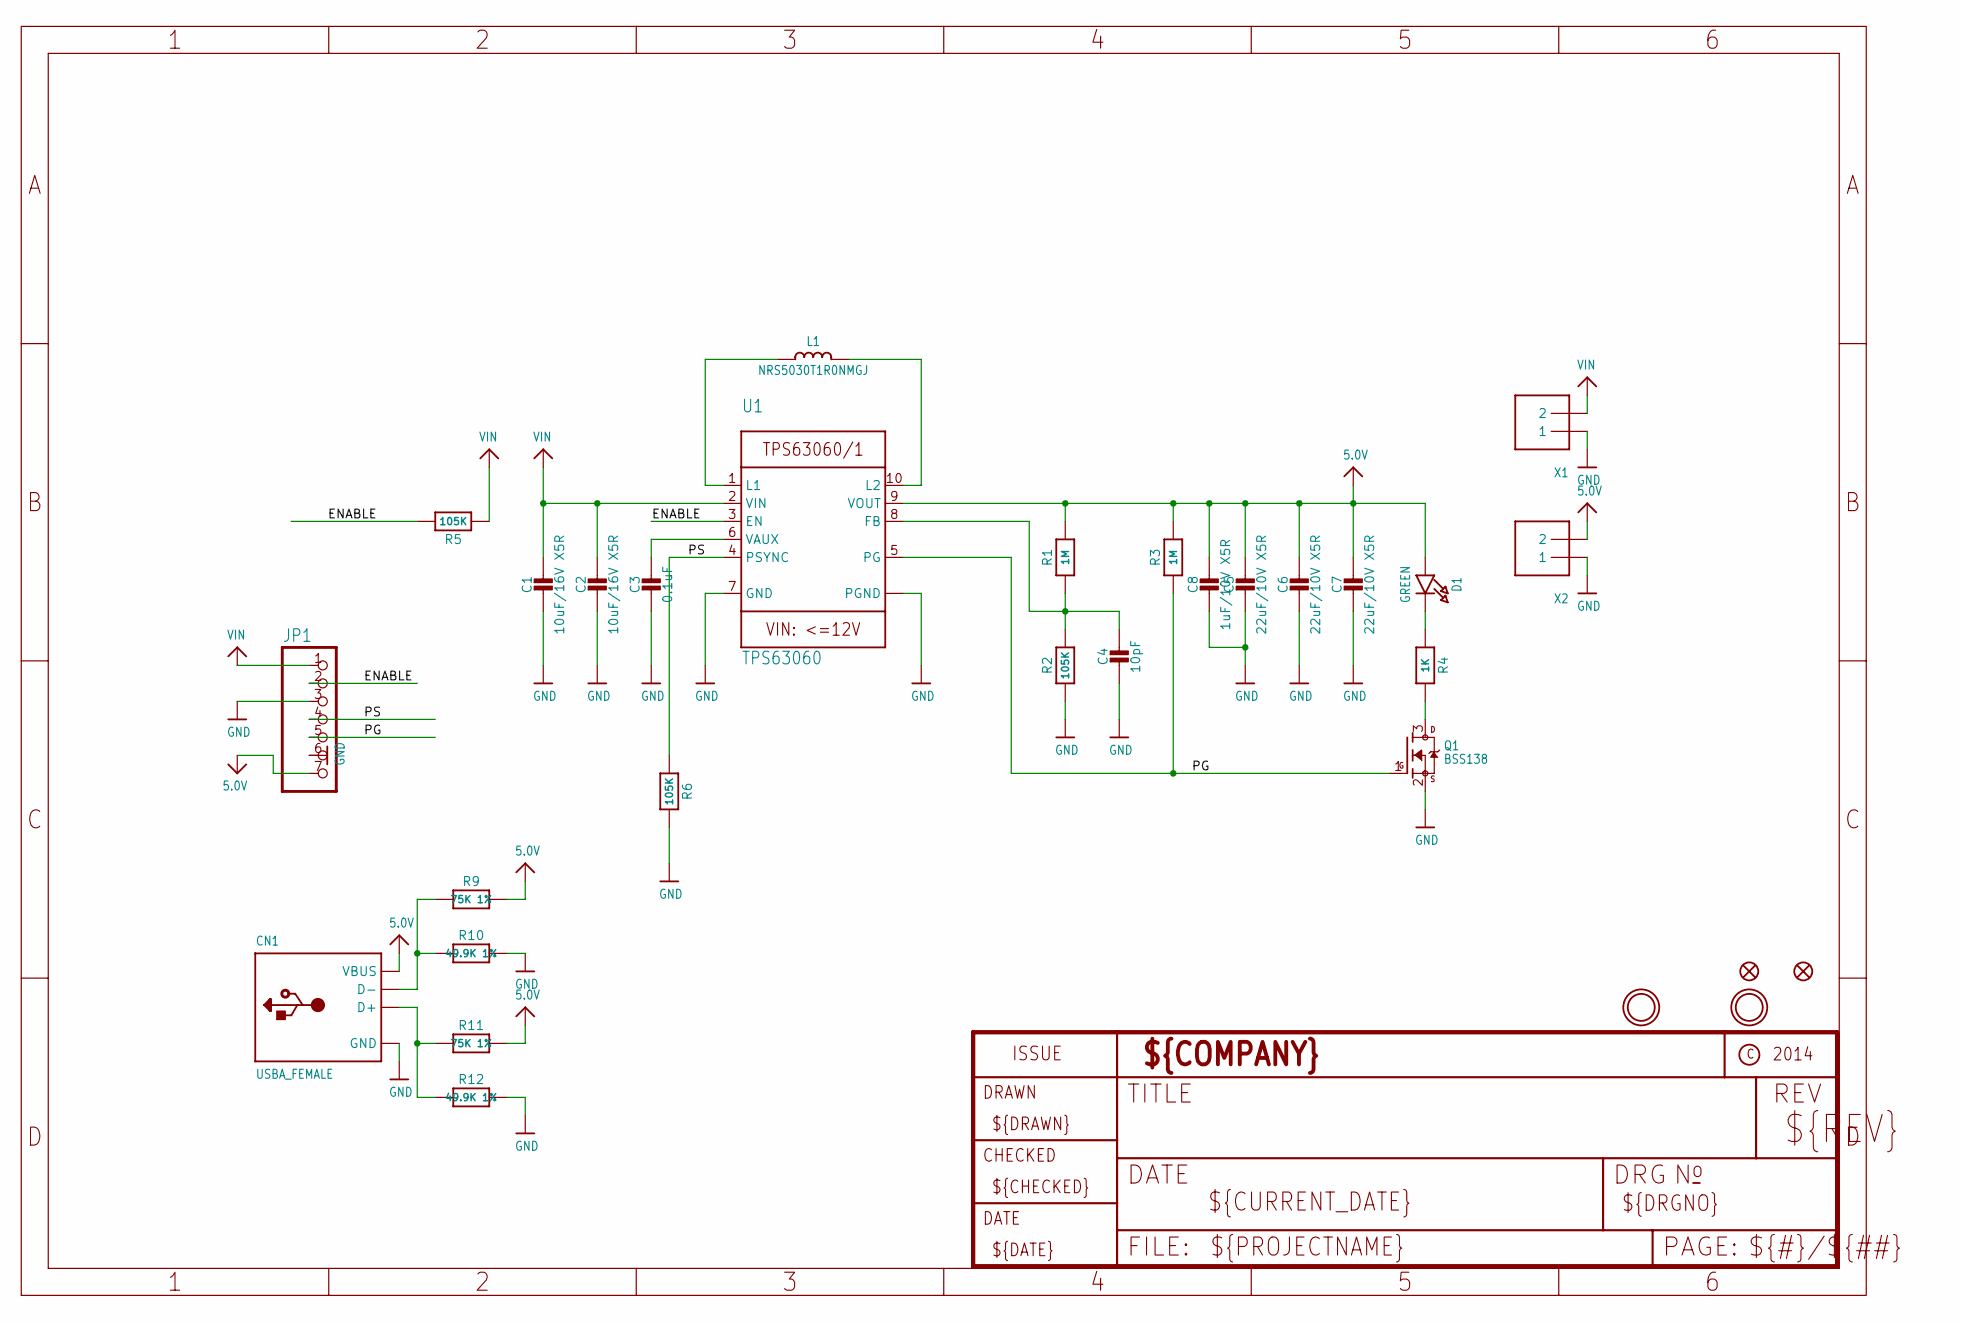
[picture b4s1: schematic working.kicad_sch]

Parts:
C1, C2: 10uF/16V X5R; 0805-NO
C3: 0.1uF; 0805-NO
C4: 10pF; 0805-NO
C5, C6, C7: 22uF/10V X5R; 0805-NO
C8: 1uF/10V X5R; 0805-NO
CN1: USBA_FEMALE; USB_HOST-PTH
D1: GREEN; CHIPLED_0805_NOOUTLINE
FID1, FID2: FIDUCIAL""; FIDUCIAL_1MM
JP1: HEADER-1X770MIL; 1X07_ROUND_70
L1: NRS5030T1R0NMGJ; INDUCTOR_5X5MM_TDK_VLC5045
Q1: BSS138; SOT23-WIDE
R1, R3: 1M; 0805-NO
R2, R5, R6: 105K; 0805-NO
R4: 1K; 0805-NO
R9, R11: 75K 1%; 0805-NO
R10, R12: 49.9K 1%; 0805-NO
U1: TPS63060; PWSON-N10
U$15, U$17: MOUNTINGHOLE2.5; MOUNTINGHOLE_2.5_PLATED
X1, X2: TERMBLOCK_1X2; TERMBLOCK_1X2-3.5MM

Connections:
5.0V: C5.1, C6.1, C7.1, C8.1, CN1.VBUS, D1.A, JP1.7, R1.2, R3.2, R9.2, R11.2, U1.9 (VOUT), X2.2
D+: CN1.D+, R11.1, R12.1
D-: CN1.D-, R9.1, R10.1
ENABLE: JP1.2, R5.2, U1.3 (EN)
GND: C1.2, C2.2, C3.2, C4.2, C5.2, C6.2, C7.2, C8.2, CN1.GND, JP1.3, JP1.6, Q1.2 (S), R2.1, R6.2, R10.2, R12.2, U1.7 (GND), U1.THERMAL@1 (PGND), U1.THERMAL@5 (PGND), U1.THERMAL@6 (PGND), U1.THERMAL@7 (PGND), U1.THERMAL@8 (PGND), U1.THERMAL@9 (PGND), U1.THERMAL@10 (PGND), U1.THERMAL@11 (PGND), U1.THERMAL@12 (PGND), U1.THERMAL@13 (PGND), U1.THERMAL@14 (PGND), X1.1, X2.1
unnamed: L1.P$1 (1), U1.1 (L1)
unnamed: L1.P$2 (2), U1.10 (L2)
unnamed: C3.1, U1.6 (VAUX)
unnamed: D1.C, R4.1
unnamed: C4.1, R1.1, R2.2, U1.8 (FB)
unnamed: Q1.3 (D), R4.2
PG: JP1.5, Q1.1 (G), R3.1, U1.5 (PG)
PS: JP1.4, R6.1, U1.4 (PSYNC)
VIN: C1.1, C2.1, JP1.1, R5.1, U1.2 (VIN), X1.2

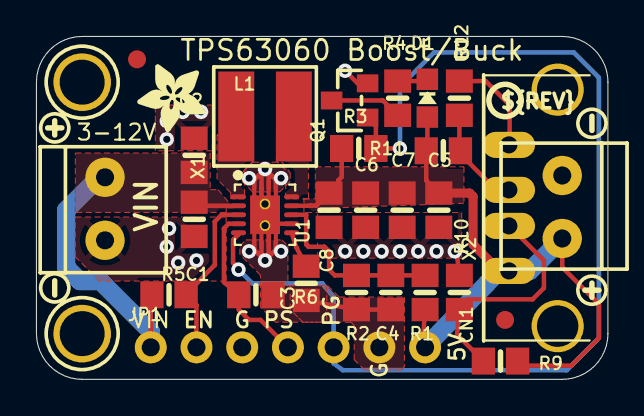
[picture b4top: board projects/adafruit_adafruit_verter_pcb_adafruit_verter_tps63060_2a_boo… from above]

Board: 2 copper layers, 31.8 x 19.0 mm, 37 parts (1 on the bottom side), 14 nets.

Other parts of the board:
U$22, U$23: SYMBOL_PLUS
U$24, U$25: SYMBOL_MINUS
U$27: ADAFRUIT_3.5MM
U$37: VERTERLOGO
U$38: PCBFEAT-REV-040

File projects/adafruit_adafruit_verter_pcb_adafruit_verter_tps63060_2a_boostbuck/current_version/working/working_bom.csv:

"Id";"Designator";"Footprint";"Quantity";"Designation";"Supplier and ref";
1;"R11,R9";"0805-NO";2;"75K 1%";;;
2;"R5,R6,R2";"0805-NO";3;"105K";;;
3;"U$23,U$22";"SYMBOL_PLUS";2;"";;;
4;"R12,R10";"0805-NO";2;"49.9K 1%";;;
5;"X1,X2";"TERMBLOCK_1X2-3.5MM";2;"";;;
6;"C5,C6,C7";"0805-NO";3;"22uF/10V X5R";;;
7;"C4";"0805-NO";1;"10pF";;;
8;"R3,R1";"0805-NO";2;"1M";;;
9;"CN1";"USB_HOST-PTH";1;"USBA_FEMALE";;;
10;"C8";"0805-NO";1;"1uF/10V X5R";;;
11;"D1";"CHIPLED_0805_NOOUTLINE";1;"GREEN";;;
12;"U$15,U$17";"MOUNTINGHOLE_2.5_PLATED";2;"MOUNTINGHOLE2.5";;;
13;"U$38";"PCBFEAT-REV-040";1;"";;;
14;"C2,C1";"0805-NO";2;"10uF/16V X5R";;;
15;"Q1";"SOT23-WIDE";1;"BSS138";;;
16;"U$24,U$25";"SYMBOL_MINUS";2;"";;;
17;"FID2,FID1";"FIDUCIAL_1MM";2;"FIDUCIAL""";;;
18;"U1";"PWSON-N10";1;"TPS63060";;;
19;"L1";"INDUCTOR_5X5MM_TDK_VLC5045";1;"NRS5030T1R0NMGJ ";;;
20;"JP1";"1X07_ROUND_70";1;"";;;
21;"R4";"0805-NO";1;"1K";;;
22;"U$27";"ADAFRUIT_3.5MM";1;"";;;
23;"C3";"0805-NO";1;"0.1uF";;;
24;"U$37";"VERTERLOGO";1;"";;;
